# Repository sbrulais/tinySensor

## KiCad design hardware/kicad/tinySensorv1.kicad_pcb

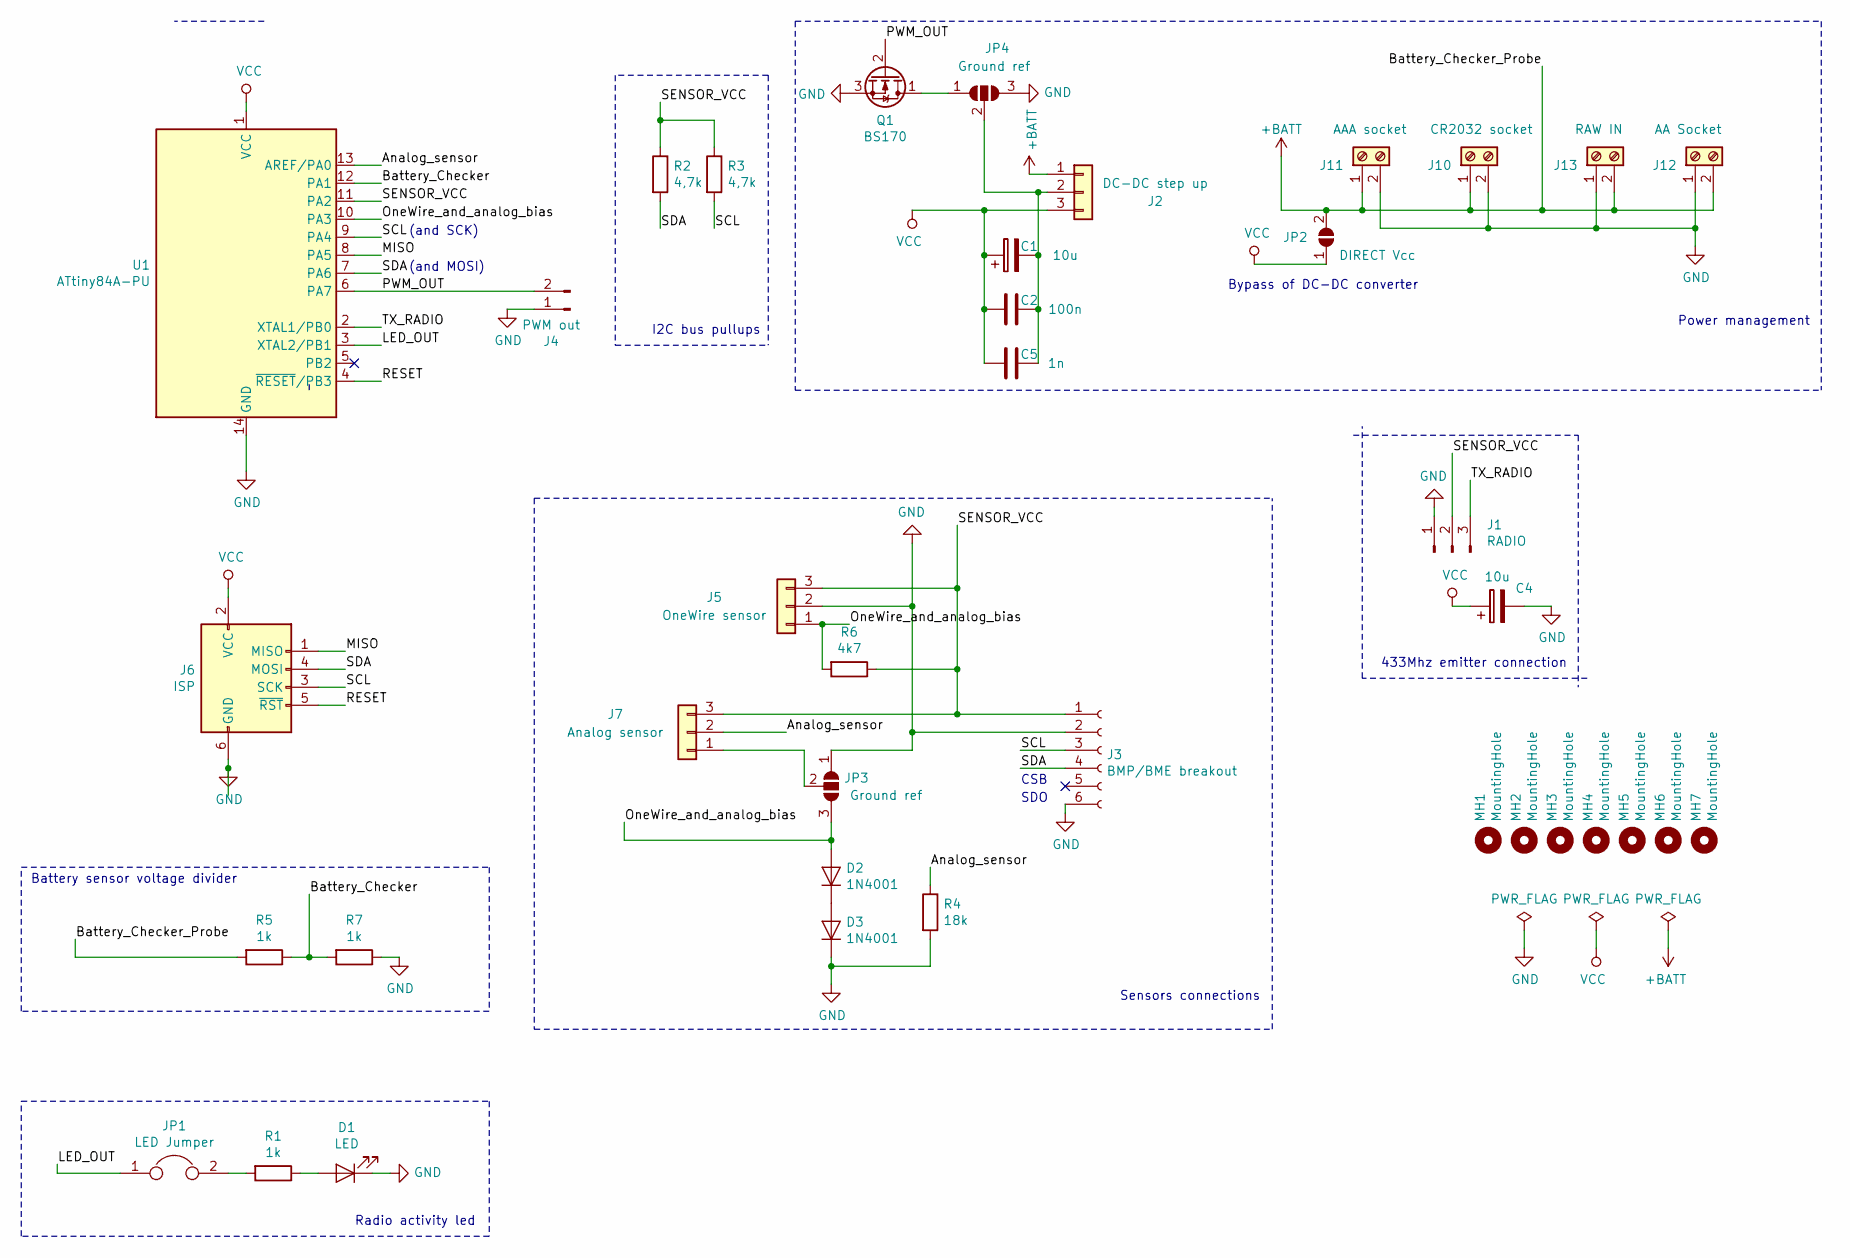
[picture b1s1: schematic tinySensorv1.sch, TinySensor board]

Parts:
C1, C4: 10u; CP_Radial_D5.0mm_P2.50mm
C2: 100n; C_Rect_L7.0mm_W2.0mm_P5.00mm
C5: 1n; CP_Radial_Tantal_D4.5mm_P2.50mm
D1: LED; LED_D1.8mm_W3.3mm_H2.4mm
D2, D3: 1N4001; D_DO-34_SOD68_P2.54mm_Vertical_AnodeUp
J1: RADIO; PinHeader_1x03_P2.54mm_Vertical
J2: DC-DC step up; PinHeader_1x03_P2.54mm_Vertical
J3: BMP/BME breakout; BMx280_breakout
J4: PWM out; PinHeader_1x02_P2.54mm_Vertical
J5: OneWire sensor; PinHeader_1x03_P2.54mm_Vertical
J6: ISP; ICSP_SOCKET_MINI_2x3
J7: Analog sensor; PinHeader_1x03_P2.54mm_Vertical
J10: CR2032 socket; BatteryHolder_Keystone_106_1x21mm
J11: AAA socket; BatteryHolder_Keystone_2466_1xAAA
J12: AA Socket; BatteryHolder_MPD_BH-18650-PC2
J13: RAW IN; TerminalBlock_bornier-2_P5.08mm
JP1: LED Jumper; PinHeader_1x02_P2.54mm_Vertical
JP2: DIRECT Vcc; SolderJumper-2_P1.3mm_Open_TrianglePad1.0x1.5mm
JP3, JP4: Ground ref; SolderJumper-3_P1.3mm_Open_Pad1.0x1.5mm_NumberLabels
MH1, MH2, MH3, MH4, MH5, MH6, MH7: MountingHole; MountingHole_2.5mm
Q1: BS170; TO-92_Inline
R1, R5, R7: 1k; R_Axial_DIN0204_L3.6mm_D1.6mm_P7.62mm_Horizontal
R2, R3: 4,7k; R_Axial_DIN0204_L3.6mm_D1.6mm_P7.62mm_Horizontal
R4: 18k; R_Axial_DIN0204_L3.6mm_D1.6mm_P7.62mm_Horizontal
R6: 4k7; R_Axial_DIN0204_L3.6mm_D1.6mm_P7.62mm_Horizontal
U1: ATtiny84A-PU; DIP-14_W7.62mm

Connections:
+BATT: J2.1, J10.1, J11.1, J12.2, J13.2, JP2.2 (B), R5.2
/Analog_sensor: J7.2, R4.1, U1.13 (AREF/PA0)
/Battery_Checker: R5.1, R7.2, U1.12 (PA1)
/LED_OUT: JP1.1, U1.3 (XTAL2/PB1)
/MISO: J6.1 (MISO), U1.8 (PA5)
/OneWire_and_analog_bias: D2.2 (A), J5.1, JP3.3 (B), R6.2, U1.10 (PA3)
/PWM_OUT: J4.2, Q1.2 (G), U1.6 (PA7)
/RESET: J6.5 (~RST), U1.4 (~RESET~/PB3)
/SCL: J3.3, J6.3 (SCK), R3.2, U1.9 (PA4)
/SDA: J3.4, J6.4 (MOSI), R2.2, U1.7 (PA6)
/SENSOR_VCC: J1.2, J3.1, J5.3, J7.3, R2.1, R3.1, R6.1, U1.11 (PA2)
/TX_RADIO: J1.3, U1.2 (XTAL1/PB0)
GND: C4.2, D1.1 (K), D3.1 (K), J1.1, J3.2, J3.6, J4.1, J5.2, J6.6 (GND), J10.2, J11.2, J12.1, J13.1, JP3.1 (A), JP4.3 (B), Q1.3 (S), R4.2, R7.1, U1.14 (GND)
unnamed: C1.2, C2.1, C5.1, J2.2, JP4.2 (C)
unnamed: D1.2 (A), R1.1
unnamed: D2.1 (K), D3.2 (A)
unnamed: J7.1, JP3.2 (C)
unnamed: JP1.2, R1.2
unnamed: JP4.1 (A), Q1.1 (D)
VCC: C1.1, C2.2, C4.1, C5.2, J2.3, J6.2 (VCC), JP2.1 (A), U1.1 (VCC)

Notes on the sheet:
SDO
CSB
Power management
I2C bus pullups
433Mhz emitter connection
(and SCK)
(and MOSI)
Sensors connections
Radio activity led
Bypass of DC-DC converter
Battery sensor voltage divider

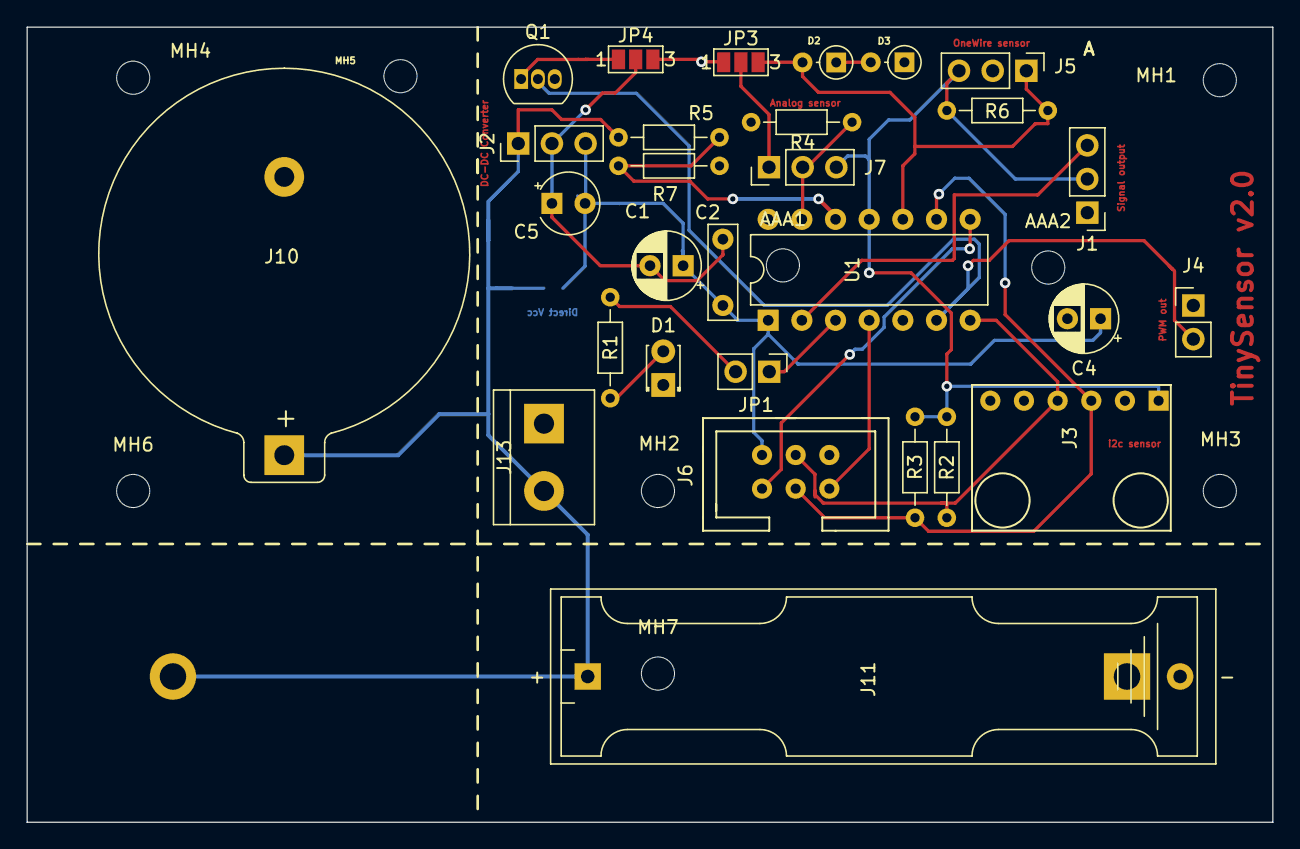
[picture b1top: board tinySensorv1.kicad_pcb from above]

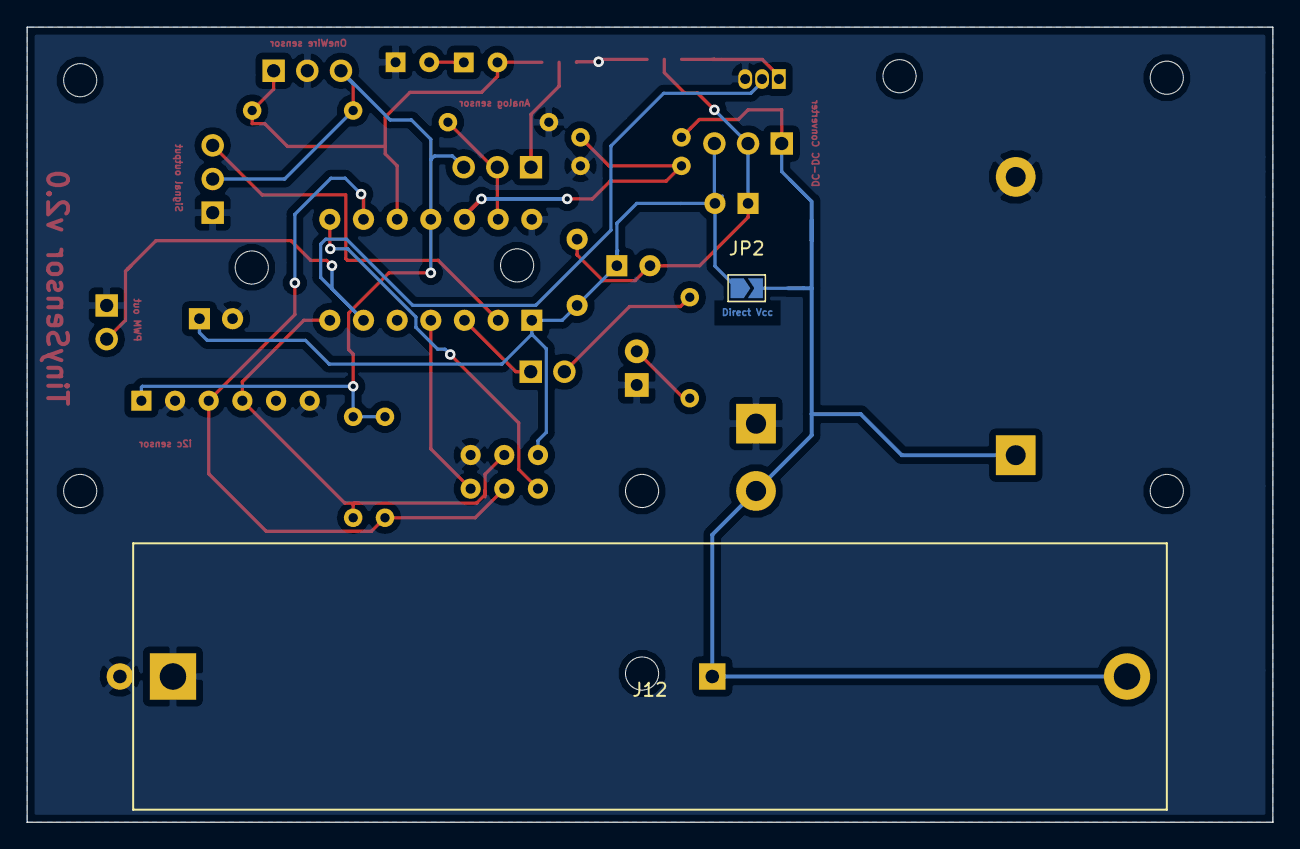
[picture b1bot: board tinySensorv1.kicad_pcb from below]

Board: 2 copper layers, 94.0 x 60.0 mm, 40 parts (2 on the bottom side), 20 nets.

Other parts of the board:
AAA1, AAA2: MountingHole; MountingHole_2.5mm

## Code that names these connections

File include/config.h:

/*
 * This file is part of the TinySensor distribution (https://github.com/arcadien/TinySensor)
 *
 * Copyright (c) 2019 Aurélien Labrosse
 *
 * This program is free software: you can redistribute it and/or modify
 * it under the terms of the GNU General Public License as published by
 * the Free Software Foundation, version 3.
 *
 * This program is distributed in the hope that it will be useful, but
 * WITHOUT ANY WARRANTY; without even the implied warranty of
 * MERCHANTABILITY or FITNESS FOR A PARTICULAR PURPOSE. See the GNU
 * General Public License for more details.
 *
 * You should have received a copy of the GNU General Public License
 * along with this program. If not, see <http://www.gnu.org/licenses/>.
 */

#pragma once

#include <inttypes.h>

// sleep 32s between each sample and
// emission
#define SLEEP_TIME_IN_SECONDS (8 * 4)

#define LED_PIN PB1
#define PWM_PIN PA7
#define TX_RADIO_PIN PB0
#define RADIO_POWER_PIN PA2
#define BAT_SENSOR_PIN PA1


/* 
* actual value for 1v1 internal ref,
* which have to be checked for each MCU
* \see https://provideyourown.com/2012/secret-arduino-voltmeter-measure-battery-voltage/
*
*
* Briefly, the reference can be obtained by 
* `internal1.1Ref = 1.1 * Vcc1 (per voltmeter) / Vcc2 (per readVcc() function)`
*/
#define ACTUAL_1V1_REF_MV 1100.

#ifdef BOARD_USES_3V3_STEPUP
#define ACTUAL_VCC_MV 3280.
#else
#define ACTUAL_VCC_MV readVcc()
#endif

// Sensors
#define USE_BMP280
//#define USE_BME280
//#define USE_DS18B20

#if defined(USE_BMP280) or defined(USE_BME280)
#define USE_I2C
#endif

const uint8_t OREGON_ID = SENSOR_ID;
const uint8_t OREGON_TYPE[] = SENSOR_TYPE;

/*
 * MODE_0 0 // Temperature only [THN132N]
 * MODE_1 1 // Temperature + Humidity [THGR2228N]
 * MODE_2 2 // Temperature + Humidity + Baro() [BTHR918N]
 */
// #define OREGON_MODE MODE_1

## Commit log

2020-01-20 new form
2020-02-09 feat: Now able to sense and emit battery level
    * VBatt voltage is sent using the X10 protocol
2020-02-16 feat: Last enhancements from hardware testing
    * Full LM35 support: <0 temp with diode support
    * 433Mhz emitter is powered by SENSOR_VCC
    * Enhanced layout
2020-02-20 layout enhancements
2020-02-24 feat: Allow shutdown of DCDC stepup
2021-04-30 Created eagle project
2021-04-30 Schematics redrawn, work in progress
